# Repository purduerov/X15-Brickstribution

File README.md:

# Readme for X15-Brickstribution

Whenever you make a new part, download the datasheet and save it here _**and**_ with the part in the parts library

Always pull other people's changes before beginning to work
`git pull`

Be sure to push your changes after  working on them. Run:
1. `git add .` to add any files in this directory or a subdirectory
or `git add -u` to add any modified files
2. (Optional) `git clean -nX` to see what ignored files can be removed
	`git clean -fX` removes ignored files (Eagle backups)
3. `git commit -m "helpful commit message"` with a description of the work that you did
4. `git push` to push your work to github

Other helpful commands
* `git status` says information about modified and staged files
* `git log` shows the recent commits of the repository
* `git log filename.extension` show the recent commits for just that file
* `git checkout first-couple-letter-of-commit-id` lets you go back to a previous version
* `git checkout master` brings you back to the latest commit
* `git tag` lists the tags
* `git tag -a orderX -m "the version of the board placed for the X'th order"` tag a specific commit
* `git push --tags` needed to push tags to remote
* `git show orderX` show the commit log for the given tag
* `git checkout orderX` go back and interact with the files at the tagged commit

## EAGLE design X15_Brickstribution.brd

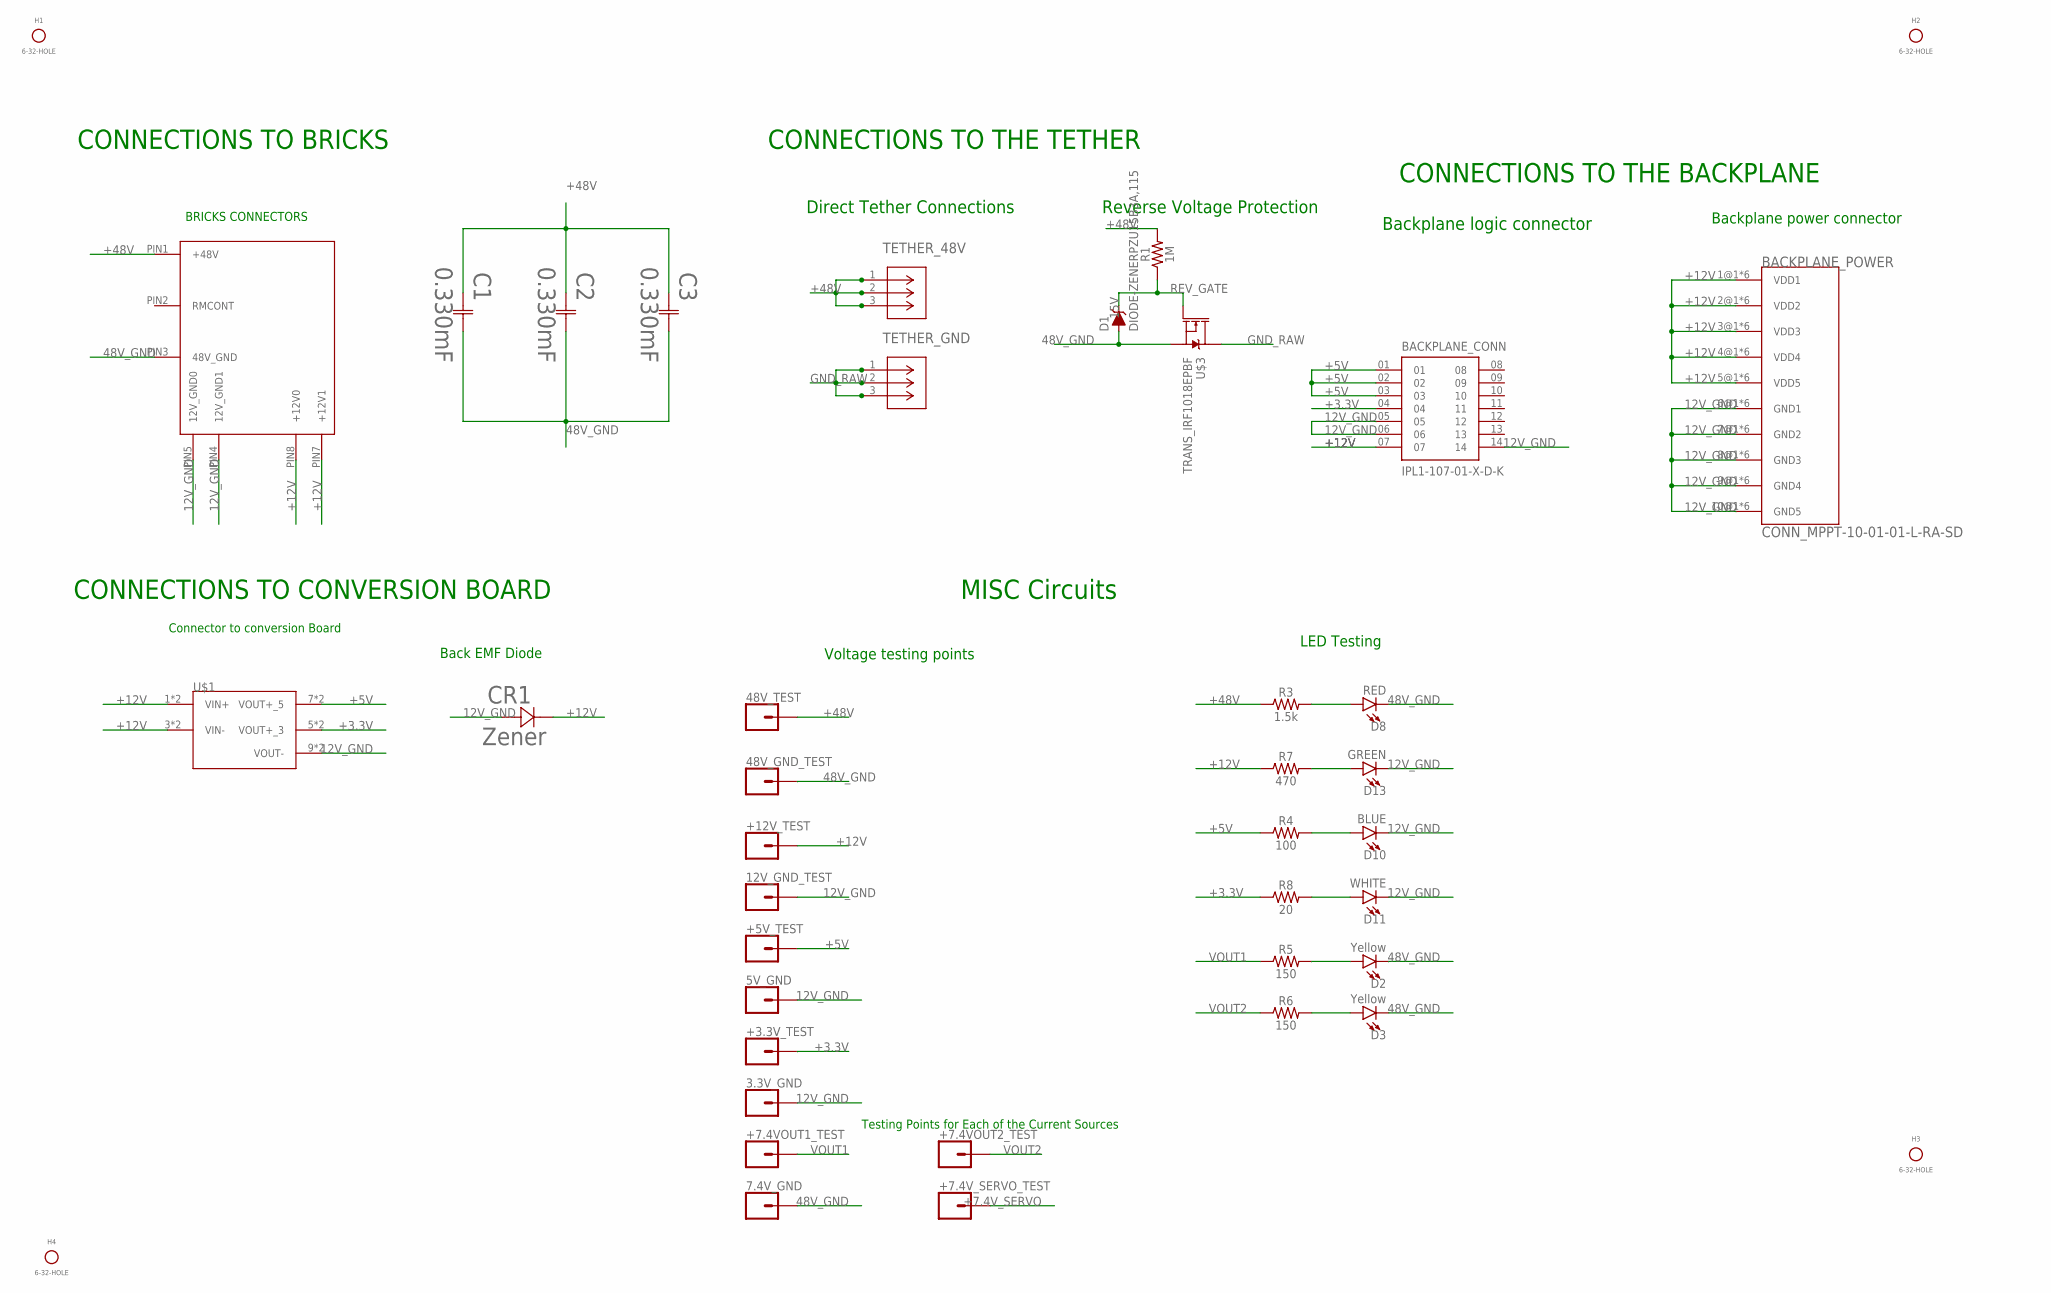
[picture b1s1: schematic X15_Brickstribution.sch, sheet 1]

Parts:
3.3V_GND, 5V_GND, 7.4V_GND, 12V_GND_TEST, 48V_GND_TEST, 48V_TEST: CONN_01; 1X01
+3.3V_TEST, +5V_TEST, +7.4VOUT1_TEST, +7.4VOUT2_TEST, +7.4V_SERVO_TEST, +12V_TEST: CONN_01; 1X01
BACKPLANE_CONN: IPL1-107-01-X-D-K; SAMTEC_IPL1-107-01-X-D-K
BACKPLANE_POWER: CONN_MPPT-10-01-01-L-RA-SD; MPPT-10-01-01-L-RA-SD
C1, C2, C3: 0.330mF; CAP_MZR_JA0_NIP-M
CR1: Zener; DIODE_DO-214AA_4P38X3P62_MCC-M
D1: DIODE-ZENERPZU15B3A,115; SOD-323
D2, D3: Yellow; LED-0603
D8: RED; LED-0603
D10: BLUE; LED-0603
D11: WHITE; LED-0603
D13: GREEN; LED-0603
H1, H2, H3, H4: 6-32-HOLE
R1: 1M; 0603
R3: 1.5k; 0603
R4: 100; 0603
R5, R6: 150; 0603
R7: 470; 0603
R8: 20; 0603
TETHER_48V: 796636-3(TETHER); CON3_P5MM_VER_TERM-BLK_TYC
TETHER_GND: 796636-3(TETHER); CON3_P5MM_VER_TERM-BLK_TYC
U$1: CONN_DISTRIBUTION_TO_CONVERSION; TSW-105-05-G-S(D-C)
U$2: CONN_BMR480_CONNECTOR; BMR480_CONNECTOR
U$3: TRANS_IRF1018EPBF; D2PAK

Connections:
12V_GND: 3.3V_GND.1, 5V_GND.1, 12V_GND_TEST.1, BACKPLANE_CONN.05, BACKPLANE_CONN.06, BACKPLANE_CONN.14, BACKPLANE_POWER.6@1 (GND1), BACKPLANE_POWER.6@2 (GND1), BACKPLANE_POWER.6@3 (GND1), BACKPLANE_POWER.6@4 (GND1), BACKPLANE_POWER.6@5 (GND1), BACKPLANE_POWER.6@6 (GND1), BACKPLANE_POWER.7@1 (GND2), BACKPLANE_POWER.7@2 (GND2), BACKPLANE_POWER.7@3 (GND2), BACKPLANE_POWER.7@4 (GND2), BACKPLANE_POWER.7@5 (GND2), BACKPLANE_POWER.7@6 (GND2), BACKPLANE_POWER.8@1 (GND3), BACKPLANE_POWER.8@2 (GND3), BACKPLANE_POWER.8@3 (GND3), BACKPLANE_POWER.8@4 (GND3), BACKPLANE_POWER.8@5 (GND3), BACKPLANE_POWER.8@6 (GND3), BACKPLANE_POWER.9@1 (GND4), BACKPLANE_POWER.9@2 (GND4), BACKPLANE_POWER.9@3 (GND4), BACKPLANE_POWER.9@4 (GND4), BACKPLANE_POWER.9@5 (GND4), BACKPLANE_POWER.9@6 (GND4), BACKPLANE_POWER.10@1 (GND5), BACKPLANE_POWER.10@2 (GND5), BACKPLANE_POWER.10@3 (GND5), BACKPLANE_POWER.10@4 (GND5), BACKPLANE_POWER.10@5 (GND5), BACKPLANE_POWER.10@6 (GND5), CR1.2, D10.C, D11.C, D13.C, U$1.9 (VOUT-), U$1.10 (VOUT-), U$2.PIN4 (12V_GND1), U$2.PIN5 (12V_GND0)
48V_GND: 7.4V_GND.1, 48V_GND_TEST.1, C1.2, C2.2, C3.2, D1.A, D2.C, D3.C, D8.C, U$2.PIN3 (48V_GND), U$3.2 (S); also elsewhere on the board
+3.3V: +3.3V_TEST.1, BACKPLANE_CONN.04, R8.1, U$1.5 (VOUT+_3), U$1.6 (VOUT+_3)
+5V: +5V_TEST.1, BACKPLANE_CONN.01, BACKPLANE_CONN.02, BACKPLANE_CONN.03, R4.1, U$1.7 (VOUT+_5), U$1.8 (VOUT+_5)
+7.4V_SERVO: +7.4V_SERVO_TEST.1; also elsewhere on the board
+12V: +12V_TEST.1, BACKPLANE_CONN.07, BACKPLANE_POWER.1@1 (VDD1), BACKPLANE_POWER.1@2 (VDD1), BACKPLANE_POWER.1@3 (VDD1), BACKPLANE_POWER.1@4 (VDD1), BACKPLANE_POWER.1@5 (VDD1), BACKPLANE_POWER.1@6 (VDD1), BACKPLANE_POWER.2@1 (VDD2), BACKPLANE_POWER.2@2 (VDD2), BACKPLANE_POWER.2@3 (VDD2), BACKPLANE_POWER.2@4 (VDD2), BACKPLANE_POWER.2@5 (VDD2), BACKPLANE_POWER.2@6 (VDD2), BACKPLANE_POWER.3@1 (VDD3), BACKPLANE_POWER.3@2 (VDD3), BACKPLANE_POWER.3@3 (VDD3), BACKPLANE_POWER.3@4 (VDD3), BACKPLANE_POWER.3@5 (VDD3), BACKPLANE_POWER.3@6 (VDD3), BACKPLANE_POWER.4@1 (VDD4), BACKPLANE_POWER.4@2 (VDD4), BACKPLANE_POWER.4@3 (VDD4), BACKPLANE_POWER.4@4 (VDD4), BACKPLANE_POWER.4@5 (VDD4), BACKPLANE_POWER.4@6 (VDD4), BACKPLANE_POWER.5@1 (VDD5), BACKPLANE_POWER.5@2 (VDD5), BACKPLANE_POWER.5@3 (VDD5), BACKPLANE_POWER.5@4 (VDD5), BACKPLANE_POWER.5@5 (VDD5), BACKPLANE_POWER.5@6 (VDD5), CR1.1, R7.1, U$1.1 (VIN+), U$1.2 (VIN+), U$1.3 (VIN-), U$1.4 (VIN-), U$2.PIN7 (+12V1), U$2.PIN8 (+12V0)
+48V: 48V_TEST.1, C1.1, C2.1, C3.1, R1.2, R3.1, TETHER_48V.1, TETHER_48V.2, TETHER_48V.3, U$2.PIN1 (+48V); also elsewhere on the board
GND_RAW: TETHER_GND.1, TETHER_GND.2, TETHER_GND.3, U$3.3 (D)
unnamed: D8.A, R3.2
unnamed: D10.A, R4.2
unnamed: D11.A, R8.2
unnamed: D3.A, R6.2
unnamed: D2.A, R5.2
unnamed: D13.A, R7.2
REV_GATE: D1.C, R1.1, U$3.1 (G)
VOUT1: +7.4VOUT1_TEST.1, R5.1; also elsewhere on the board
VOUT2: +7.4VOUT2_TEST.1, R6.1; also elsewhere on the board

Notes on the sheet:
CONNECTIONS TO BRICKS
BRICKS CONNECTORS
CONNECTIONS TO CONVERSION BOARD
Back EMF Diode
CONNECTIONS TO THE TETHER
Reverse Voltage Protection
Direct Tether Connections
MISC Circuits
Voltage testing points
Backplane logic connector
Backplane power connector
CONNECTIONS TO THE BACKPLANE
Connector to conversion Board
LED Testing
Testing Points for Each of the Current Sources

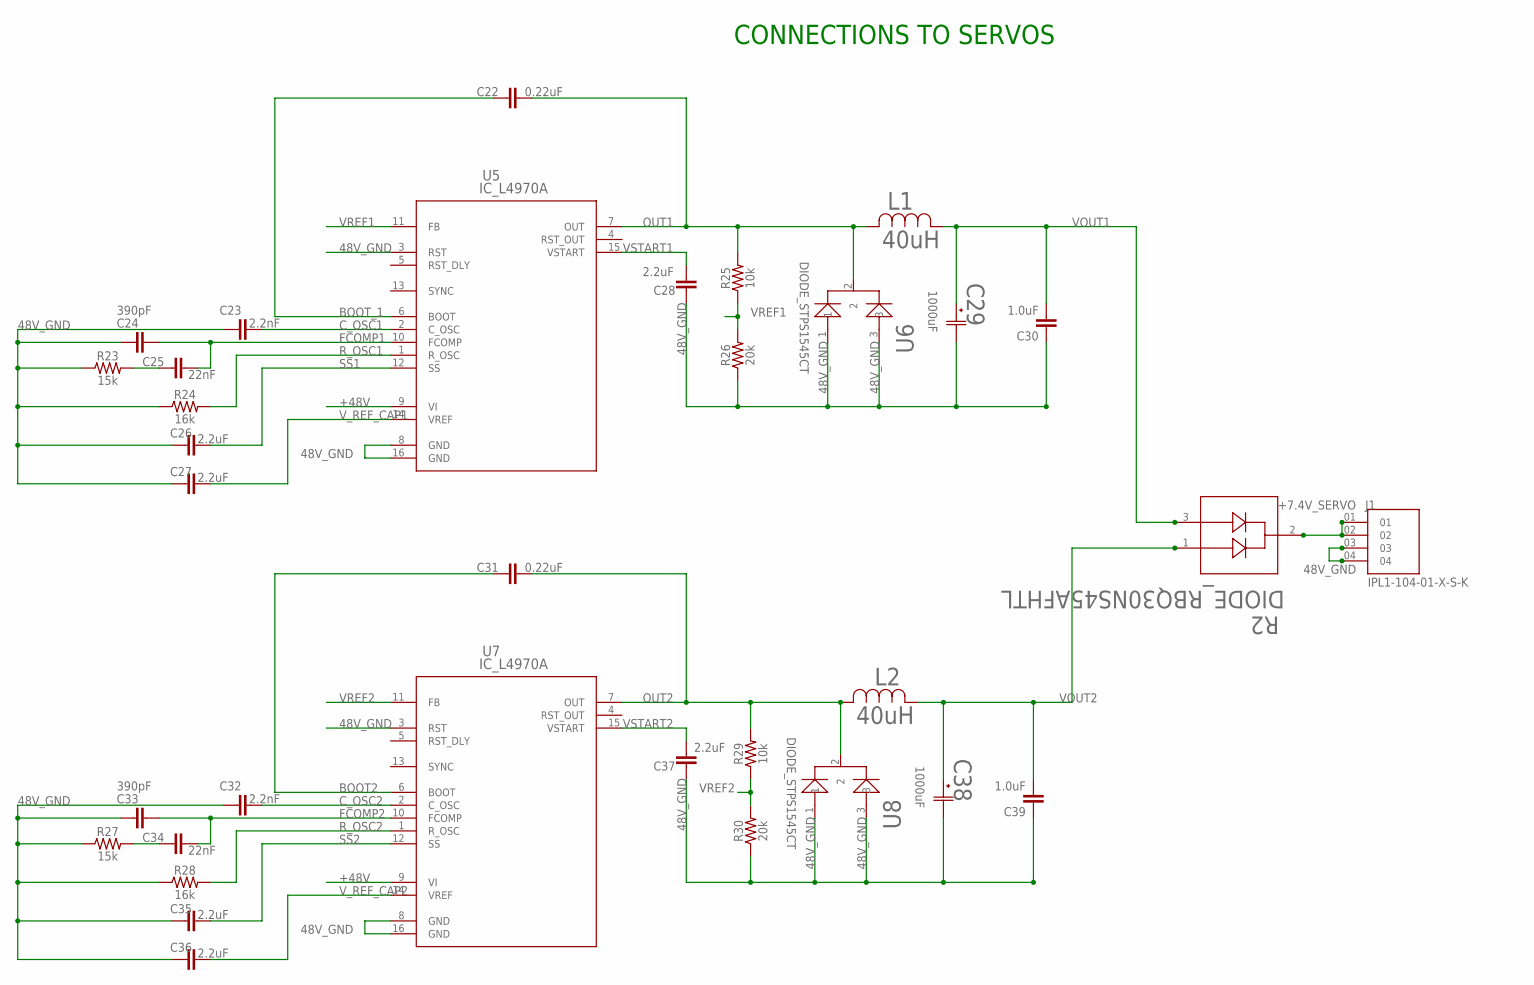
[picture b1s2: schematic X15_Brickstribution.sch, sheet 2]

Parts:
C22, C31: 0.22uF; 0603
C23, C32: 2.2nF; 0603
C24, C33: 390pF; 0603
C25, C34: 22nF; 0603
C26, C27, C28, C35, C36, C37: 2.2uF; 0603
C29, C38: 1000uF; CAP_PC_10X12P7_NCH-M
C30, C39: 1.0uF; 0603
J1: IPL1-104-01-X-S-K; SAMTEC_IPL1-104-01-X-S-K
L1, L2: 40uH; IND_23XX-V_53_53
R2: DIODE_RBQ30NS45AFHTL; TRANS_R5009FNJ_ROM
R23, R27: 15k; 0603
R24, R28: 16k; 0603
R25, R29: 10k; 0603
R26, R30: 20k; 0603
U5, U7: IC_L4970A; MULTIWATT15_V_STM
U6, U8: DIODE_STPS1545CT; TO-220AB_STM

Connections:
48V_GND: C23.1, C24.1, C26.1, C27.1, C28.1, C29.2, C30.1, C32.1, C33.1, C35.1, C36.1, C37.1, C38.2, C39.1, J1.03, J1.04, R23.1, R24.1, R26.1, R27.1, R28.1, R30.1, U5.3 (RST), U5.8 (GND), U5.16 (GND), U6.1, U6.3, U7.3 (RST), U7.8 (GND), U7.16 (GND), U8.1, U8.3; also elsewhere on the board
+7.4V_SERVO: J1.01, J1.02, R2.2; also elsewhere on the board
+48V: U5.9 (VI), U7.9 (VI); also elsewhere on the board
BOOT2: C31.1, U7.6 (BOOT)
BOOT_1: C22.1, U5.6 (BOOT)
C_OSC1: C23.2, U5.2 (C_OSC)
C_OSC2: C32.2, U7.2 (C_OSC)
FCOMP1: C24.2, C25.2, U5.10 (FCOMP)
FCOMP2: C33.2, C34.2, U7.10 (FCOMP)
unnamed: C25.1, R23.2
unnamed: C34.1, R27.2
OUT1: C22.2, L1.2, R25.2, U5.7 (OUT), U6.2
OUT2: C31.2, L2.2, R29.2, U7.7 (OUT), U8.2
R_OSC1: R24.2, U5.1 (R_OSC)
R_OSC2: R28.2, U7.1 (R_OSC)
SS1: C26.2, U5.12 (SS)
SS2: C35.2, U7.12 (SS)
VOUT1: C29.1, C30.2, L1.1, R2.3; also elsewhere on the board
VOUT2: C38.1, C39.2, L2.1, R2.1; also elsewhere on the board
VREF1: R25.1, R26.2, U5.11 (FB)
VREF2: R29.1, R30.2, U7.11 (FB)
VSTART1: C28.2, U5.15 (VSTART)
VSTART2: C37.2, U7.15 (VSTART)
V_REF_CAP1: C27.2, U5.14 (VREF)
V_REF_CAP2: C36.2, U7.14 (VREF)

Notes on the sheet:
CONNECTIONS TO SERVOS

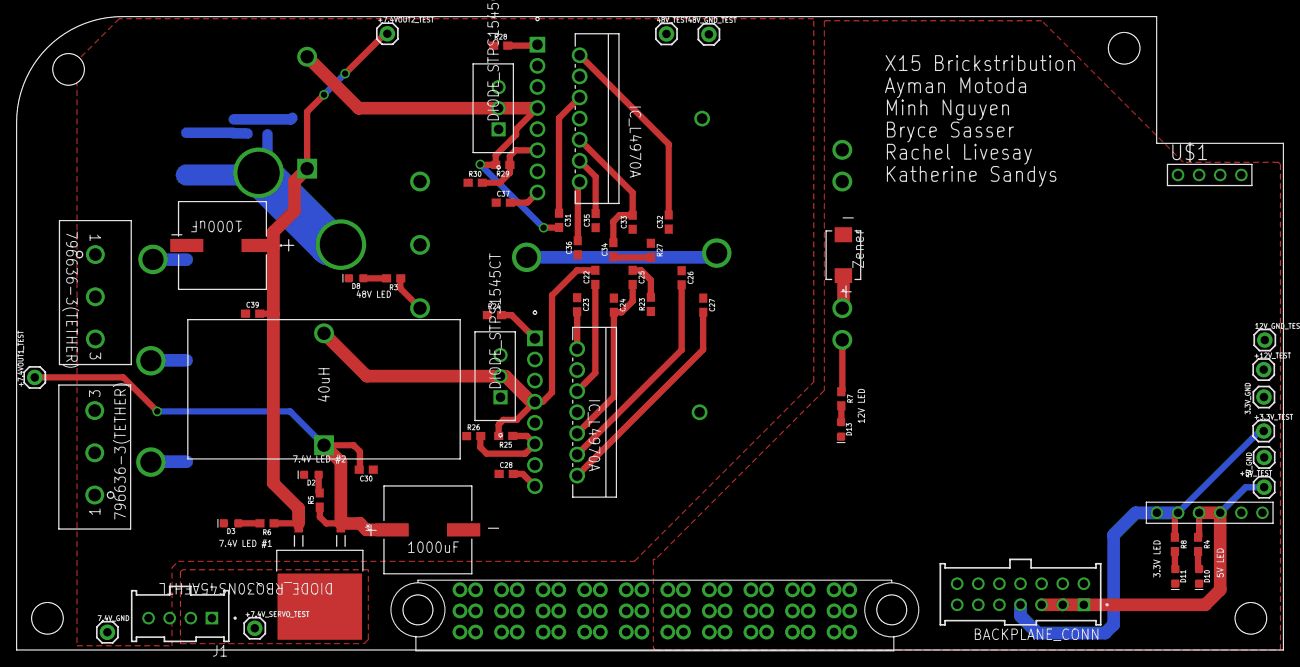
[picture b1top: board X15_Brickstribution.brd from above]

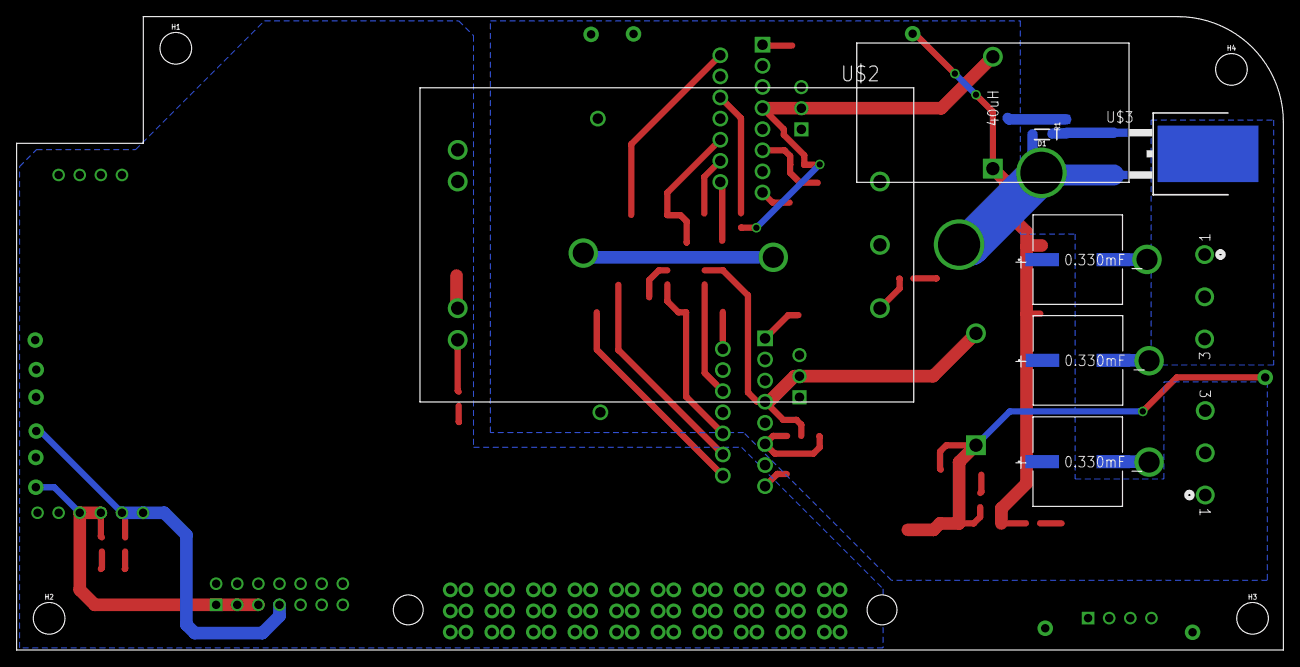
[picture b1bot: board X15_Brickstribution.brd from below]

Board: 2 copper layers, 152.4 x 76.2 mm, 75 parts (12 on the bottom side), 37 nets.

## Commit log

2022-10-08 git commit -a
2022-10-08 Schematic V1
2022-10-08 Schematic V1 - Added Backplane Connections
2022-10-15 Schematic Revision V1
2022-10-19 Cleaned all backup files and updated schematic for revisions v1
2022-10-20 Revision V3 Schematic - LED's added for current source
2022-10-20 board dimensions
2022-10-22 48V Components Added to PCB
2022-11-05 Board & Schematic Review Iteration
2022-11-09 Changed inductor out and reconfigured traces.
2022-11-10 Moved placement of resistors.
2022-11-12 Changed polygons and connections to reference voltage
2022-11-17 Before getting absolutely torn apart by Alumni Review
2022-12-01 In progress board
2022-12-01 Finished version of alternative layout
2022-12-03 Alumni Revisions Implemented
2022-12-03 Fixed Tracing Errors
2022-12-08 Final Iteration of Layout
2022-12-08 Grant Approval
2022-12-10 Revision before implementing Samtec Brick Connectors
2023-01-07 Fixed a small wire stub to pass DRC

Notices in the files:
parts and their libraries:
SparkFun-Resistors: Licensing: Creative Commons ShareAlike 4.0 International - https://creativecommons.org/licenses/by-sa/4.0
COPYRIGHT: Copyright (C) 2022 Ultra Librarian. All rights reserved.
